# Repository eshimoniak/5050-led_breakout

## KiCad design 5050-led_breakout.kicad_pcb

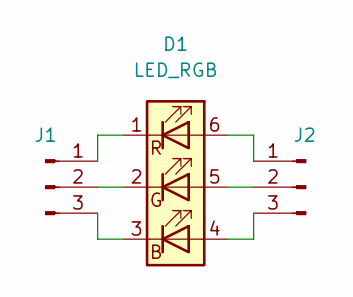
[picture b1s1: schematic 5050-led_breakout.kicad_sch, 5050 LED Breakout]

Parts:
D1: LED_RGB; LED_RGB_5050-6
J1, J2: 1x3 Header; PinHeader_1x03_P2.54mm_Vertical

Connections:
unnamed: D1.1 (RK), J1.1
unnamed: D1.2 (GK), J1.2
unnamed: D1.3 (BK), J1.3
unnamed: D1.6 (RA), J2.1
unnamed: D1.5 (GA), J2.2
unnamed: D1.4 (BA), J2.3

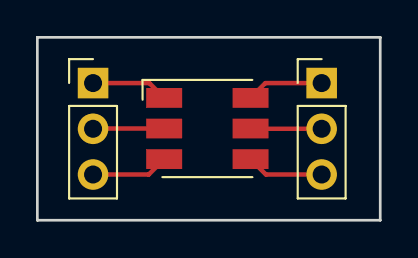
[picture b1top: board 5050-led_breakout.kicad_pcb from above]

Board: 2 copper layers, 19.1 x 10.2 mm, 3 parts (0 on the bottom side), 6 nets.

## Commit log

2023-02-12 Updated to KiCad version 7
2023-02-12 Fixed edge layer type
2023-02-12 Gerber output
